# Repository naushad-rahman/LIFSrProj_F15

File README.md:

**Repository for Senior Project ECEn 490 Section 1, Fall 2015, BYU**

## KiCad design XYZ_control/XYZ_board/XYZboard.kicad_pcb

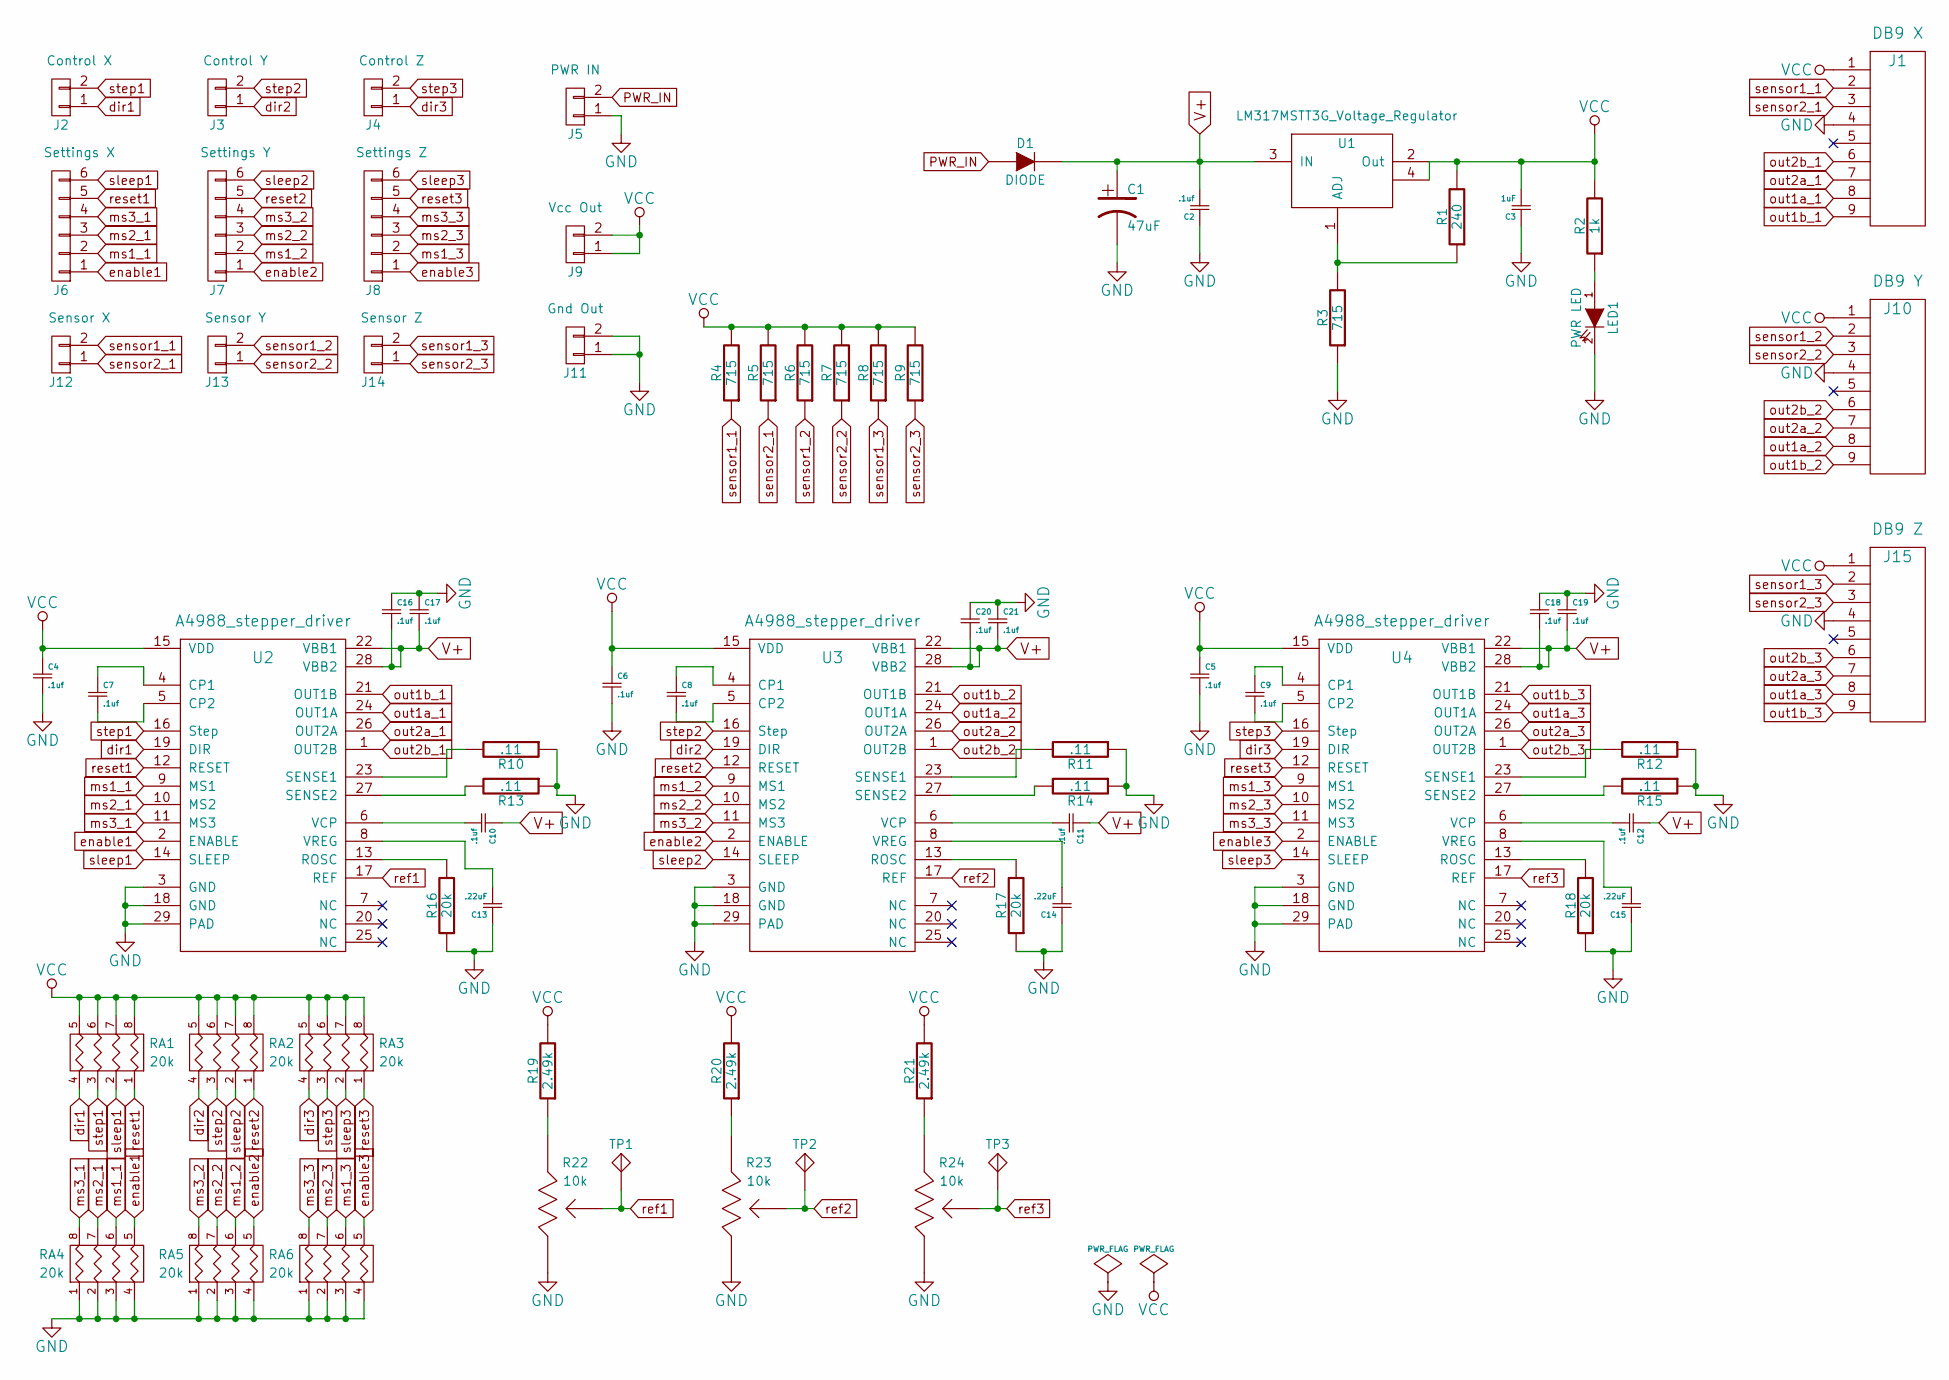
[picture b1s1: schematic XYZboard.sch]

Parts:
C1: 47uF; PCE3929CT-ND
C2, C4, C5, C6, C7, C8, C9, C10, C11, C12, C16, C17, C18, C19, C20, C21: .1uf; C_0603_HandSoldering
C3: 1uF; C_0603_HandSoldering
C13, C14, C15: .22uF; C_0603_HandSoldering
D1: DIODE; SD2010S040S3R0
J1: DB9 X; DB9MD
J2: Control X; Pin_Header_Straight_1x02
J3: Control Y; Pin_Header_Straight_1x02
J4: Control Z; Pin_Header_Straight_1x02
J5: PWR IN; Pin_Header_Straight_1x02
J6: Settings X; Pin_Header_Straight_1x06
J7: Settings Y; Pin_Header_Straight_1x06
J8: Settings Z; Pin_Header_Straight_1x06
J9: Vcc Out; Pin_Header_Straight_1x02
J10: DB9 Y; DB9MD
J11: Gnd Out; Pin_Header_Straight_1x02
J12: Sensor X; Pin_Header_Straight_1x02
J13: Sensor Y; Pin_Header_Straight_1x02
J14: Sensor Z; Pin_Header_Straight_1x02
J15: DB9 Z; DB9MD
LED1: PWR LED; LGR971-KN-1
R1: 240; R_0603_HandSoldering
R2: 1k; R_0603_HandSoldering
R3, R4, R5, R6, R7, R8, R9: 715; R_0603_HandSoldering
R10, R11, R12, R13, R14, R15: .11; R_1206_HandSoldering
R16, R17, R18: 20k; R_0603_HandSoldering
R19, R20, R21: 2.49k; R_0603_HandSoldering
R22, R23, R24: 10k; TC33X-103ECT-ND
RA1, RA2, RA3, RA4, RA5, RA6: 20k; CAT16-203J4LFCT-ND
TP1, TP2, TP3: Test_point; Measurement_Point_Square-SMD-Pad_Big
U1: LM317MSTT3G_Voltage_Regulator; voltage_regulator_sot223
U2, U3, U4: A4988_stepper_driver; Qfn_28_A4988_with_thermal_vias

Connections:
GND: C1.2, C2.1, C3.1, C4.2, C5.2, C6.2, C13.1, C14.1, C15.1, C16.1, C17.1, C18.1, C19.1, C20.1, C21.1, J1.4, J5.1, J10.4, J11.1, J11.2, J15.4, LED1.2 (K), R3.1, R10.1, R11.1, R12.1, R13.1, R14.1, R15.1, R16.1, R17.1, R18.1, R22.3, R23.3, R24.3, RA4.1, RA4.2, RA4.3, RA4.4, RA5.1, RA5.2, RA5.3, RA5.4, RA6.1, RA6.2, RA6.3, RA6.4, U2.3 (GND), U2.18 (GND), U2.29 (PAD), U3.3 (GND), U3.18 (GND), U3.29 (PAD), U4.3 (GND), U4.18 (GND), U4.29 (PAD)
unnamed: C7.1, U2.4 (CP1)
unnamed: C7.2, U2.5 (CP2)
unnamed: C8.1, U3.4 (CP1)
unnamed: C8.2, U3.5 (CP2)
unnamed: C9.1, U4.4 (CP1)
unnamed: C9.2, U4.5 (CP2)
unnamed: C10.2, U2.6 (VCP)
unnamed: C11.2, U3.6 (VCP)
unnamed: C12.2, U4.6 (VCP)
unnamed: C13.2, U2.8 (VREG)
unnamed: C14.2, U3.8 (VREG)
unnamed: C15.2, U4.8 (VREG)
unnamed: LED1.1 (A), R2.1
unnamed: R1.1, R3.2, U1.1 (ADJ)
unnamed: R10.2, U2.23 (SENSE1)
unnamed: R11.2, U3.23 (SENSE1)
unnamed: R12.2, U4.23 (SENSE1)
unnamed: R13.2, U2.27 (SENSE2)
unnamed: R14.2, U3.27 (SENSE2)
unnamed: R15.2, U4.27 (SENSE2)
unnamed: R16.2, U2.13 (ROSC)
unnamed: R17.2, U3.13 (ROSC)
unnamed: R18.2, U4.13 (ROSC)
unnamed: R19.1, R22.1
unnamed: R20.1, R23.1
unnamed: R21.1, R24.1
PWR_IN: D1.1 (A), J5.2
V+: C1.1, C2.2, C10.1, C11.1, C12.1, C16.2, C17.2, C18.2, C19.2, C20.2, C21.2, D1.2 (K), U1.3 (IN), U2.22 (VBB1), U2.28 (VBB2), U3.22 (VBB1), U3.28 (VBB2), U4.22 (VBB1), U4.28 (VBB2)
VCC: C3.2, C4.1, C5.1, C6.1, J1.1, J9.1, J9.2, J10.1, J15.1, R1.2, R2.2, R4.2, R5.2, R6.2, R7.2, R8.2, R9.2, R19.2, R20.2, R21.2, RA1.5 (R4), RA1.6 (R3), RA1.7 (R2), RA1.8 (R1), RA2.5 (R4), RA2.6 (R3), RA2.7 (R2), RA2.8 (R1), RA3.5 (R4), RA3.6 (R3), RA3.7 (R2), RA3.8 (R1), U1.2 (Out), U1.4, U2.15 (VDD), U3.15 (VDD), U4.15 (VDD)
dir1: J2.1, RA1.4, U2.19 (DIR)
dir2: J3.1, RA2.4, U3.19 (DIR)
dir3: J4.1, RA3.4, U4.19 (DIR)
enable1: J6.1, RA4.5 (R4), U2.2 (ENABLE)
enable2: J7.1, RA5.5 (R4), U3.2 (ENABLE)
enable3: J8.1, RA6.5 (R4), U4.2 (ENABLE)
ms1_1: J6.2, RA4.6 (R3), U2.9 (MS1)
ms1_2: J7.2, RA5.6 (R3), U3.9 (MS1)
ms1_3: J8.2, RA6.6 (R3), U4.9 (MS1)
ms2_1: J6.3, RA4.7 (R2), U2.10 (MS2)
ms2_2: J7.3, RA5.7 (R2), U3.10 (MS2)
ms2_3: J8.3, RA6.7 (R2), U4.10 (MS2)
ms3_1: J6.4, RA4.8 (R1), U2.11 (MS3)
ms3_2: J7.4, RA5.8 (R1), U3.11 (MS3)
ms3_3: J8.4, RA6.8 (R1), U4.11 (MS3)
out1a_1: J1.8, U2.24 (OUT1A)
out1a_2: J10.8, U3.24 (OUT1A)
out1a_3: J15.8, U4.24 (OUT1A)
out1b_1: J1.9, U2.21 (OUT1B)
out1b_2: J10.9, U3.21 (OUT1B)
out1b_3: J15.9, U4.21 (OUT1B)
out2a_1: J1.7, U2.26 (OUT2A)
out2a_2: J10.7, U3.26 (OUT2A)
out2a_3: J15.7, U4.26 (OUT2A)
out2b_1: J1.6, U2.1 (OUT2B)
out2b_2: J10.6, U3.1 (OUT2B)
out2b_3: J15.6, U4.1 (OUT2B)
ref1: R22.2, TP1.1, U2.17 (REF)
ref2: R23.2, TP2.1, U3.17 (REF)
ref3: R24.2, TP3.1, U4.17 (REF)
reset1: J6.5, RA1.1, U2.12 (RESET)
reset2: J7.5, RA2.1, U3.12 (RESET)
reset3: J8.5, RA3.1, U4.12 (RESET)
sensor1_1: J1.2, J12.2, R4.1
sensor1_2: J10.2, J13.2, R6.1
sensor1_3: J14.2, J15.2, R8.1
sensor2_1: J1.3, J12.1, R5.1
sensor2_2: J10.3, J13.1, R7.1
sensor2_3: J14.1, J15.3, R9.1
sleep1: J6.6, RA1.2, U2.14 (SLEEP)
sleep2: J7.6, RA2.2, U3.14 (SLEEP)
sleep3: J8.6, RA3.2, U4.14 (SLEEP)
step1: J2.2, RA1.3, U2.16 (Step)
step2: J3.2, RA2.3, U3.16 (Step)
step3: J4.2, RA3.3, U4.16 (Step)

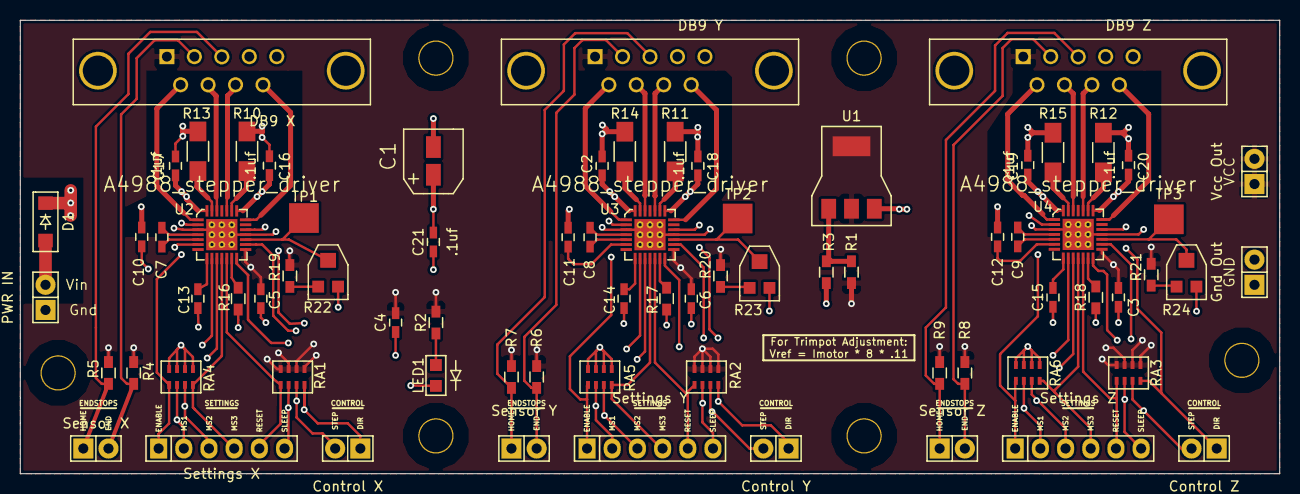
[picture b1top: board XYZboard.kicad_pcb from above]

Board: 4 copper layers, 127.0 x 45.7 mm, 81 parts (0 on the bottom side), 75 nets.

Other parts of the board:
mounting hole0_13, mounting hole0_13#2, mounting hole0_13#3, mounting hole0_13#4, mounting hole0_13#5, mounting hole0_13#6: VAL**; mounting_hole_0_13_in

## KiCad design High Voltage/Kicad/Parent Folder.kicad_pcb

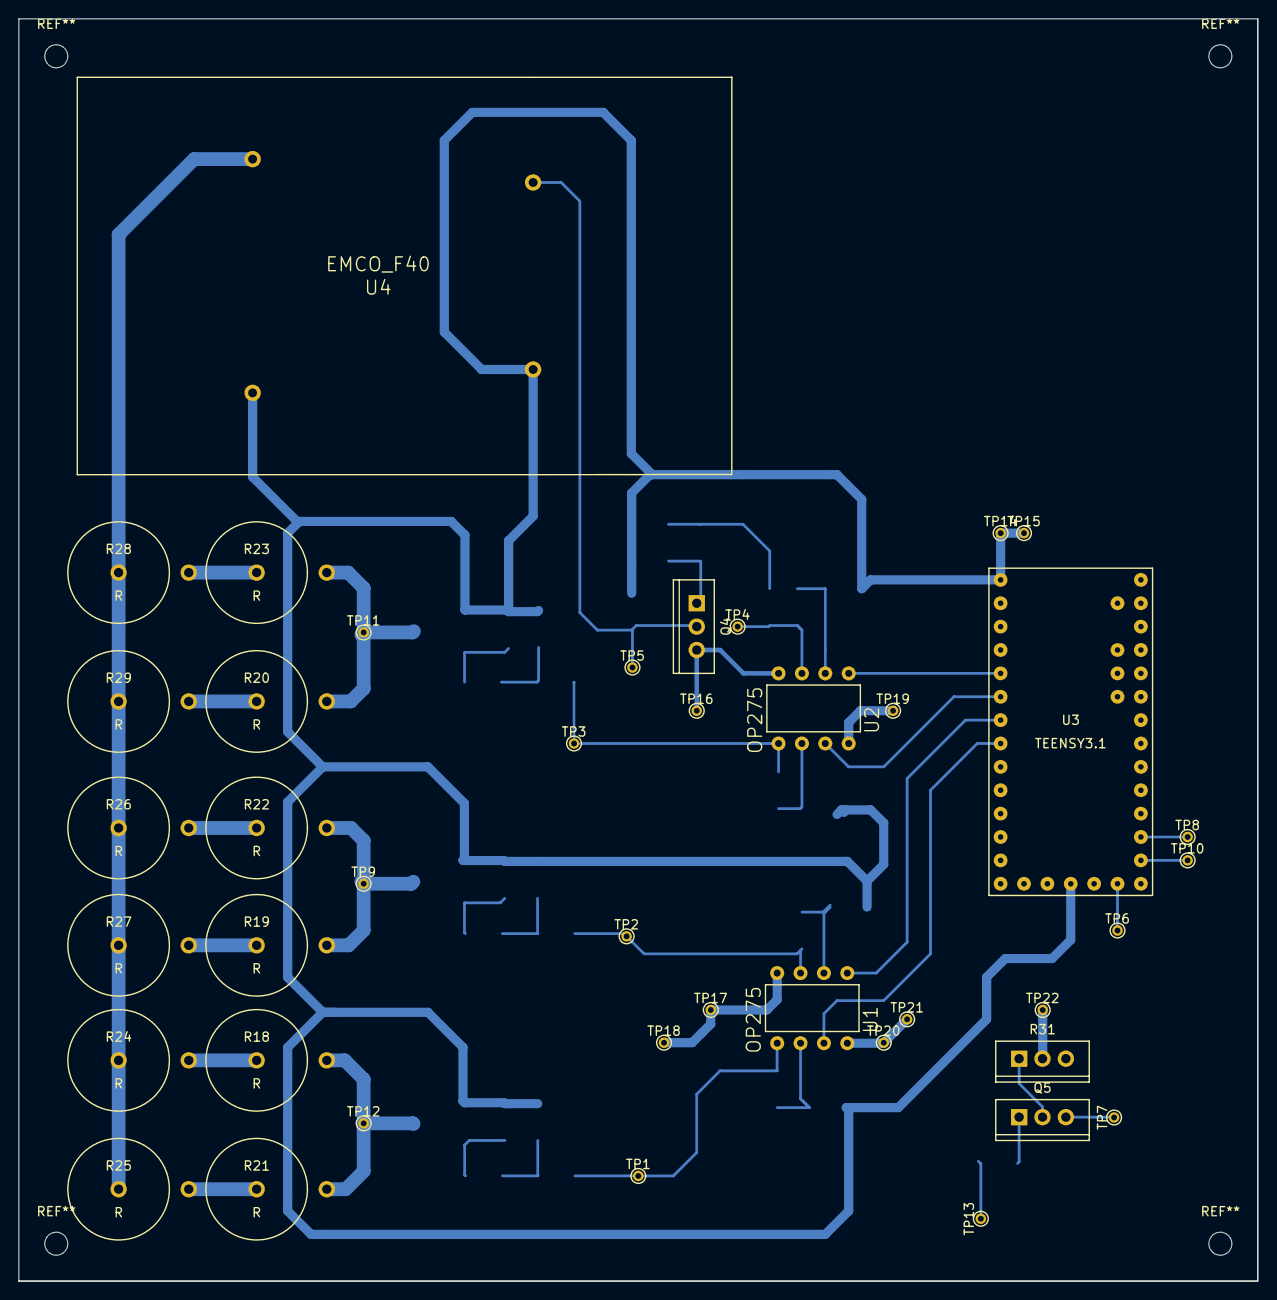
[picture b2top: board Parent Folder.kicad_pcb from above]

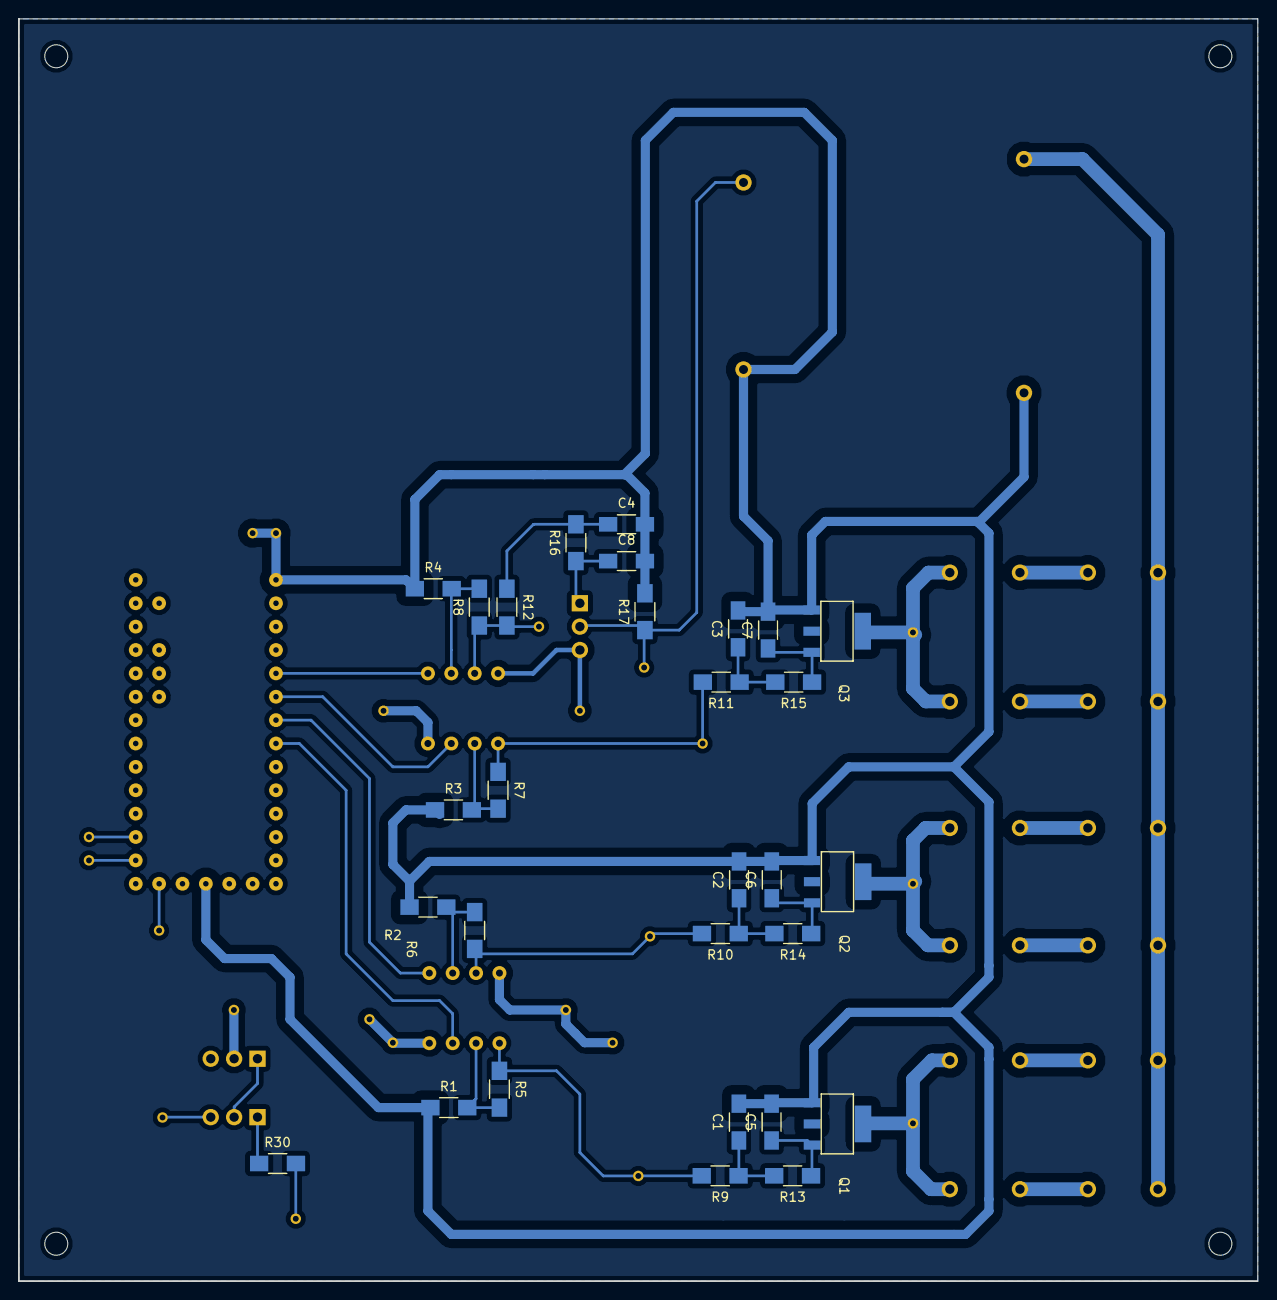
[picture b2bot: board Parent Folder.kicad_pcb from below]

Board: 2 copper layers, 134.6 x 137.2 mm, 70 parts (29 on the bottom side), 42 nets.

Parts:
C1, C2, C3, C4, C5, C6, C7, C8: C; C_1206_HandSoldering
Q1, Q2, Q3: STN0214
Q4: BUT11A; TO220_VERT
Q5: NPN; TO220_VERT
R1, R2, R3, R4, R5, R6, R7, R8, R9, R10, R11, R12, R13, R14, R15, R16, R17, R30: R; R_1206_HandSoldering
R18, R19, R20, R21, R22, R23, R24, R25, R26, R27, R28, R29: R; RES_1W
R31: Varable_Res; POT
TP1, TP2, TP3, TP4, TP5, TP6, TP7, TP8, TP9, TP10, TP11, TP12, TP13, TP14, TP15, TP16, TP17, TP18, TP19, TP20, TP21, TP22: Test_point; PINTST
U1, U2: OP275; OpAmp
U3: TEENSY3.1
U4: EMCO_F40

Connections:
+5V: R31.2, TP22.1
+12V: Q4.2, TP16.1, TP17.1, TP18.1, U1.8, U2.8
-12V: TP19.1, TP20.1, TP21.1, U1.4, U2.4
GND: C1.2, C2.2, C3.2, C4.2, C5.2, C6.2, C7.2, C8.2, Q1.1, Q2.1, Q3.1, R1.1, R2.1, R3.1, R4.1, R17.2, TP14.1, TP15.1, U3.1, U3.17, U4.2, U4.4
unnamed: C1.1, R9.1, R13.2
unnamed: C2.1, R10.1, R14.2
unnamed: C3.1, R11.1, R15.2
unnamed: C4.1, R12.1, R16.2
unnamed: C5.1, Q1.3, R13.1
unnamed: C6.1, Q2.3, R14.1
unnamed: C7.1, Q3.3, R15.1
unnamed: C8.1, Q4.1, R16.1
unnamed: Q1.2, Q1.4, R18.2, R21.2, TP12.1
unnamed: Q2.2, Q2.4, R19.2, R22.2, TP9.1
unnamed: Q3.2, Q3.4, R20.2, R23.2, TP11.1
unnamed: Q4.3, R17.1, TP5.1, U4.1
unnamed: Q5.1, R30.1
unnamed: Q5.2, TP7.1
unnamed: Q5.3, R31.1
unnamed: R1.2, R5.2, U1.2
unnamed: R2.2, R6.2, U1.6
unnamed: R3.2, R7.2, U2.2
unnamed: R4.2, R8.2, U2.6
unnamed: R5.1, R9.2, TP1.1, U1.1
unnamed: R6.1, R10.2, TP2.1, U1.7
unnamed: R7.1, R11.2, TP3.1, U2.1
unnamed: R8.1, R12.2, TP4.1, U2.7
unnamed: R18.1, R24.2
unnamed: R19.1, R27.2
unnamed: R20.1, R29.2
unnamed: R21.1, R25.2
unnamed: R22.1, R26.2
unnamed: R23.1, R28.2
unnamed: R24.1, R25.1, R26.1, R27.1, R28.1, R29.1, U4.3
unnamed: R30.2, TP13.1
unnamed: TP6.1, U3.19
unnamed: TP8.1, U3.22
unnamed: TP10.1, U3.21
unnamed: U1.3, U3.8
unnamed: U1.5, U3.7
unnamed: U2.3, U3.6
unnamed: U2.5, U3.5

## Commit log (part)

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2015-05-05 I am learning
2015-05-05 Was removed
2015-05-05 Hua created this file
2015-05-05 Hua remove his file
2015-05-13 Here are the Cad files for holding the PMT
2015-05-15 Updated the High Voltage .ino with correct pins
2015-05-15 Updated the widgets on XYZ control
2015-05-15 3D printing
2015-05-20 test file
2015-05-20 hua demo
2015-05-20 testfile deleted
2015-05-29 Files for teensy UI
2015-06-03 Code for new high voltage board
2015-06-03 removed extra cad file
2015-06-04 This is the Optical Bench
2015-06-04 Same holder, just made in openscad
2015-06-10 DSP for teensy
2015-06-12 Updated files
2015-06-12 Misnamed files
2015-06-17 DSP for the PMT
2015-06-18 New file. DAQ working
2015-06-18 Remove files
2015-06-18 Remove old DSP files
2015-06-22 LP and BP working
2015-06-22 Not needed
2015-06-29 updated DSP
2015-07-02 New implementation of DSP code
2015-07-07 Laser Driver
2015-07-07 Updated DSP: execute_BPF, loop and arrays were modified
2015-07-07 contine to test filters & add a pdf book on practical filter design
2015-07-07 calculate the bandpass filter gain at 1 kHz - yes, this method works
2015-07-07 normalize filter coefficients and test using them
2015-07-08 finish up zero-phase FIR filter notebook (150706_...)
2015-07-08 png with notes
2015-07-08 update figure showing indexing for zero-phase shift FIR filter
2015-07-08 add example with noisy data
2015-07-08 add example with no 1 kHz modulation
2015-07-09 small update
2015-07-09 Updated DSP: Removed moving average. Also we are able to see this with the Ipython Notebook
2015-07-09 Fix j so it is declared as volatile and some minor clean up of code
2015-07-09 Add impulse and pulse cases to basic filter tests in notebook
2015-07-09 Add SNR calculation to aid comparison of 1 kHz modulated and DC cases
2015-07-09 printed off PMT signal
2015-07-10 fix data file and look at data from Teensy
2015-07-10 test_BPF in Ipython notebook not working
2015-07-10 test_BPF in the ipython notebook is working now
2015-07-10 start doing incremental development of teensy & python code, basic communication works
2015-07-10 Establish simple serial communication from Teensy to python code in a notebook
2015-07-11 change format of data sent over serial by test_BPF.ino & make ipython notebook to catch and plot the data
2015-07-11 Serial port reading added to test_BPF
2015-07-11 Read data from serial port in Ipython notebook. Changed the fir filter as well in the arduino code.
2015-07-11 fix git conflicts and put my stuff in new directory
2015-07-11 remove my notebook from DSP/tests/test_BPF to avoid confusion. It is in my folder DSP/tests/test_BPF_GN_150710
2015-07-11 clean up code so it is ready for next additions
2015-07-11 found and fixed pernicious bug using impulse signal. Filter is now truly zero-phase
2015-07-11 changed test_signal so that it is always calculated in setup()
2015-07-11 added a to-do list at the end of DSP/tests/test_BPF_GN_150711/150711_read_serial_data.ipynb
2015-07-11 Clearning up
2015-07-11 Cleaning up files we don't need
2015-07-12 Cleaning up
2015-07-12 moved this file to a different location
2015-07-12 moved this file to test_BPF folder
2015-07-12 Copied files from Dr. Nordin to play with
2015-07-12 Understand what is going on with BPF. And it looks like it's working
2015-07-12 Just playing with BPF.
2015-07-12 Added a case 3 where I made a cosine from the lut
2015-07-12 Took first step with the to list here
2015-07-12 add test signal options 3-6 (lut cosine, rect puls, rect modulation of raised cosine, gaussian modulation of raised cosine)
2015-07-12 move seril.print statements to loop() from the interrupt function
2015-07-12 Added cosine multiplication, which seems to work correctly. Added low pass filter, which is having problems. Not ready to use or modify.
2015-07-13 Added code to both .ino and ipython notebook for a test for BPF with a rectangular pulse
2015-07-13 start new effort to redesign teensy code to only do sample acquisition in interrupt and make all other calls in loop()
2015-07-13 Added a rectangular impulse function to both .ino and ipython notebook
2015-07-13 All filtering works correctly
2015-07-14 restore corrupted file DSP/tests/test_filtersinloop_150713/test_filtersinloop_150713.ipynb
2015-07-14 things work up until the low pass filter. I think the problem is with doing the 2nd zero-phase filter (i.e., low pass filter). The indexing gets out of whack (at least by comparison with the working 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
2015-07-14 modify python code to do linear phase filters and test out. Works good
2015-07-14 final check in before modifying code from zero-phase to linear phase filters
2015-07-14 not working
2015-07-14 no output is generated on the serial port by the Teensy
2015-07-14 re-start from scratch, building things up systematically
2015-07-14 update .gitignore to avoid tracking files with 'copy' in their name
2015-07-14 low pass filter works. Everything is called in loop(). The low pass filter is FIR linear phase and not zero phase
2015-07-14 slight modification to code: put filter coefficient normalization inside a function
2015-07-14 HV, DC laser driver, Low pass filter
    HV and DC laser driver verified and working. Need to test the Low pass
    filter with the test vectors.
2015-07-15 Started to integrate everything but stuck at zero phase shift for BPF
2015-07-16 DC DSP - working
    The code is tested and working. See ipynb for verification.
2015-07-16 Verification of DC DSP
    Test cases and results
2015-07-22 Deleted extra stuff
    Code is repeated
2015-07-22 Updating DAQ Code
    Changing data aquisition code to control HV. Will transfer to .py file
    and run from anaconda cmd.
2015-07-22 Python code to interface with Teensy DAQ
    First steps to transferring notebook to single python
2015-07-24 Changes to output format
    Instead of sending the time and PMT output as an array of bytes, we are
    sending in plain ints and floats. Tested and working.
2015-07-24 Python Scripts for Plotting
    Instead of the using the notebook, we will use python files for data
    collection. I added buttons on the widget to control the high voltage.
2015-07-24 Adding Buttons and changing serial format
    Changed byte sending to int for time and float for PMT signal output.
    Added buttons for the widget to control the high voltage. Took this code
    and made a .py file.
2015-07-27 Analog LPF before Teensy
    To remove high frequency aliasing of noise above our sampling rate of
    10kHz
2015-07-27 Recorded results for tests for the noise
2015-07-28 PMT Raw Data Test
    Testing the RAW Data from the PMT in several scenarios. See readme.txt.
    testing folder contains csv files and pictures.
2015-07-28 New DC PMT
    Several Program options. 1-Test Array, 2-PMT raw data, 3-LPF data
2015-07-29 Correct ADC read bug
    10 bit to 12 bit resolution in analog read function.
2015-07-30 Analog Filter design to filter 5kHz
2015-07-30 Sampling Test
2015-07-30 Plot all data after experiment
    On the click of the quit button, all data will be plotted for analysis.
2015-07-30 CSV Data Plot to python script
    The script prompts the user to enter the name of the CSV file to plot.
    Run from anaconda terminal
2015-07-30 Update CSV Data Plot notebook
2015-07-30 Decrease lag
2015-08-04 Tried new filter coefficients and got a better result with Gaussian test
2015-08-04 XYZ Joystick Controller
    Get rid of junk and put in XYZ Joystick controller
2015-08-07 Changes to High Voltage
    We changed the HV to decrease sparking within the channels. This setting
    gives us 700 volts for insertion instead of 1kvolts and we don't see
    sparking.
2015-08-07 Data from Aug 7 flow tests
    Data taken from experiments to see flow in channels
2015-08-11 Add comments to code
2015-08-11 Added comments to help distinguish between high voltage parts and DSP parts
2015-08-11 Made a comment for the High voltage part of code
2015-08-11 comment for different cases in loop
2015-08-11 Laser Driver Updates
2015-08-12 Remove unneeded folder
2015-08-12 Empty directory deleted
2015-08-12 Nothing new. Just moving around files
2015-08-12 Update on after PMT circuitry
2015-09-17 Updating readme for new semester
    I copied all the code over from Spring/Summer, as we will be building
    off of their work.
2015-09-22 Update README.md
    I moved all of the code from Spring/Summer over here for us to use and build off of.
2015-09-22 Added prompt for notes on files created
    Now, when the graph is closed, a prompt will appear to ask the user to
    record some notes about the experiment. These notes are saved in
    \RecordedData\TestNotes.txt
2015-09-22 Trying to update this.
2015-10-02 More work on tags
    Tags are now saved to a .json file. Also, I adjusted the way files are
    named so that two digits are always used for months and days.
2015-10-05 getting tags worked out, adjusting date formatting.
2015-10-05 Just testing this git stuff.
2015-10-06 Added tag searching script, adjusted json tags
2015-10-06 The Python code is now correctly communicating with the Teensy!
2015-10-08 Added tag for microfluidic device number. Rewrote large chunks of teensyData.py to add multithreaded processesing. This still needs testing and debugging.
2015-10-08 Small changes to convert code from Python 3 to Python 2.7
2015-10-08 Multithreading is working!
2015-10-08 Now with more threads! ...and more missed time.
2015-10-09 Added MFD Data Logging System
2015-10-09 Example MFD Log Created
2015-10-09 Example Log
2015-10-13 Tagging and tag searcher updated.
2015-10-13 Experimenting with serial stuff
2015-10-13 Added laser characterization data and plots
2015-10-13 Serial issues are mostly better time is now an unsigned long, deques are being used instead of queues, and packets are now being sent every 125 usec. This will be improved upon in the future.
2015-10-15 Better formatting for tagging prompt.
2015-10-20 Added code to determine number of missed packets.
2015-10-20 Simulation files for DSP development
2015-10-20 Data and graphs on laser characterization at different voltages over 5 minutes
2015-10-20 Making some progress with the serial communication.
2015-10-22 working with python serial code
2015-10-23 Added recent logs
2015-10-23 Notes added
2015-10-25 Serial communication is (mostly) fixed!
2015-10-29 New Log
2015-10-29 Two-way serial communication implemented.
2015-11-03 Add readme file
2015-11-03 Trying to figure out GIT
2015-11-06 Modifications to python interface with Teensy and processing operations including data filtering
2015-11-06 Minor updates to python interface code
2015-11-06 Significant updates to python code including additional graphing capabilities and thresholding algorithms
2015-11-06 Updates on python dsp processing with log file integration
2015-11-06 Updated code with detection reporting capabilities
2015-11-06 This includes updates of Test notes and several new .csv data files
2015-11-07 updating files to be able to commit, all .csv files in /RecordedData have now been added to the .gitignore file so that they will not be revisioned and tracked in the repository
2015-11-10 Fixing bad commits and removing big .csv files
2015-11-10 Restored accidentally deleted file 20151106_083803.csv
2015-11-10 Fixing .csv data problems so the repo can be pushed to github
2015-11-12 New data acquired (.csv files not loaded to git repository) and updates on keylogger code
2015-11-18 small fixes to teensyData.py UI while reviewing code with Jared
2015-11-19 modifications to post processing and dc processing analysis ipython notebook
2015-11-19 update of ufluidics lab workstation code and data files
2015-11-20 minor alteration in ufliudics_dsp.py to change string report of processing type
2015-12-03 small fix to data logging
2015-12-08 add ipython notebook to analyze data from 12/3/15
2015-12-11 sync with computer data and minor code updates
2015-12-15 Final device log
2015-12-16 Removing outdated CAD file
2015-12-16 Create CAD
2015-12-16 CAD: uploaded current 3d files and how to run the system
